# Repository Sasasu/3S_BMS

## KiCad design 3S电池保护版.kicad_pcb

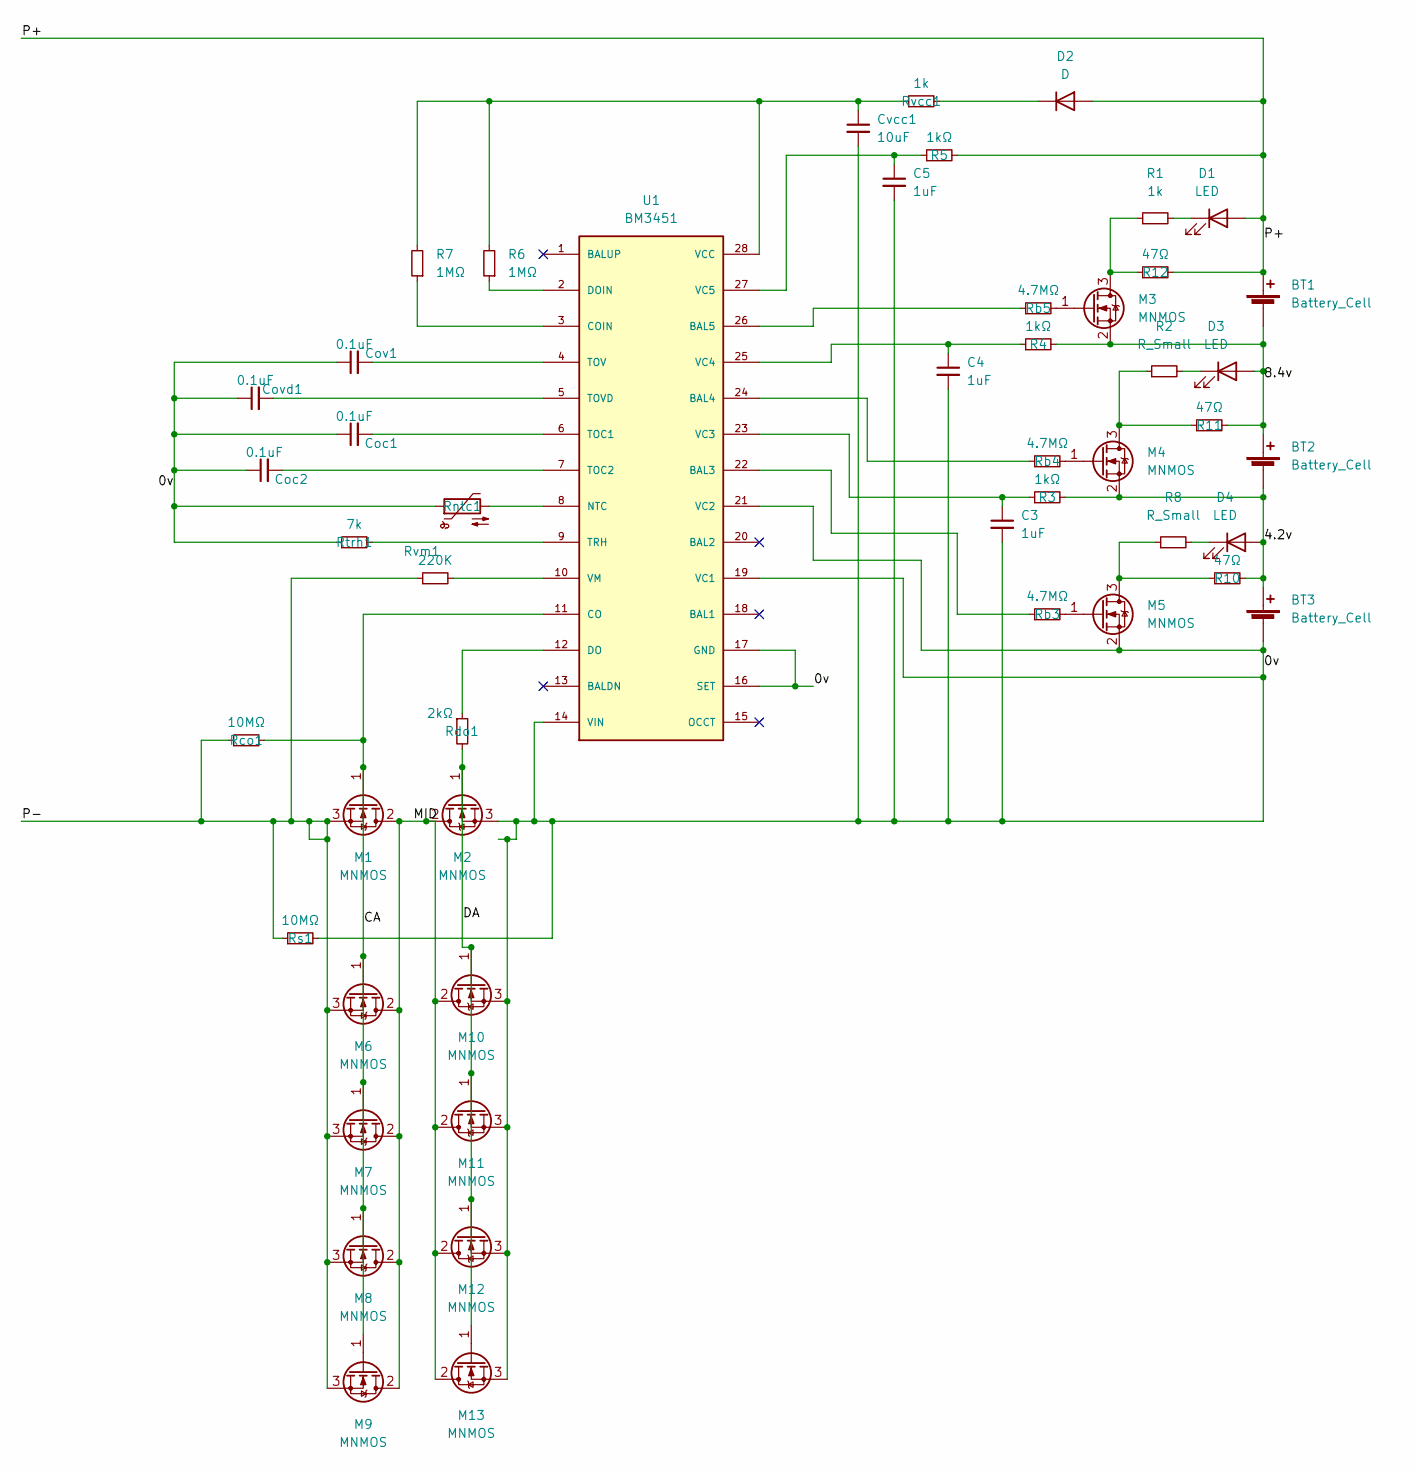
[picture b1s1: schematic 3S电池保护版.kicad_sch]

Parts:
BT1, BT2, BT3: Battery_Cell
C3, C4, C5: 1uF; C_0402_1005Metric_Pad0.74x0.62mm_HandSolder
Coc1, Coc2: 0.1uF; C_0402_1005Metric_Pad0.74x0.62mm_HandSolder
Cov1: 0.1uF; C_0402_1005Metric_Pad0.74x0.62mm_HandSolder
Covd1: 0.1uF; C_0402_1005Metric_Pad0.74x0.62mm_HandSolder
Cvcc1: 10uF; C_0402_1005Metric_Pad0.74x0.62mm_HandSolder
D1, D3, D4: LED; LED_0402_1005Metric_Pad0.77x0.64mm_HandSolder
D2: D; D_SOD-323
M1, M2, M6, M7, M8, M9, M10, M11, M12, M13: MNMOS; TO-252-2
M3, M4, M5: MNMOS; SOT-23
R1: 1k; R_0402_1005Metric_Pad0.72x0.64mm_HandSolder
R2, R8: R_Small; R_0402_1005Metric_Pad0.72x0.64mm_HandSolder
R3, R4, R5: 1kΩ; R_0402_1005Metric_Pad0.72x0.64mm_HandSolder
R6, R7: 1MΩ; R_0402_1005Metric_Pad0.72x0.64mm_HandSolder
R10, R11, R12: 47Ω; R_2512_6332Metric
Rb3, Rb4, Rb5: 4.7MΩ; R_0402_1005Metric_Pad0.72x0.64mm_HandSolder
Rco1: 10MΩ; R_0402_1005Metric_Pad0.72x0.64mm_HandSolder
Rdo1: 2kΩ; R_0402_1005Metric_Pad0.72x0.64mm_HandSolder
Rntc1: Thermistor_NTC; R_0805_2012Metric_Pad1.20x1.40mm_HandSolder
Rs1: 10MΩ; R_0402_1005Metric_Pad0.72x0.64mm_HandSolder
Rtrh1: 7k; R_0402_1005Metric_Pad0.72x0.64mm_HandSolder
Rvcc1: 1k; R_0402_1005Metric_Pad0.72x0.64mm_HandSolder
Rvm1: 220K; R_0402_1005Metric_Pad0.72x0.64mm_HandSolder
U1: BM3451; SSOP28

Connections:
/0v: BT3.2 (-), C3.2, C4.2, C5.2, Coc1.1, Coc2.1, Cov1.1, Covd1.1, Cvcc1.2, M2.3 (S), M5.2 (S), M10.3 (S), M11.3 (S), M12.3 (S), M13.3 (S), Rntc1.1, Rs1.2, Rtrh1.1, U1.14 (VIN), U1.16 (SET), U1.17 (GND), U1.19 (VC1), U1.21 (VC2)
/4.2v: BT2.2 (-), BT3.1 (+), D4.2 (A), M4.2 (S), R3.2, R10.2
/8.4v: BT1.2 (-), BT2.1 (+), D3.2 (A), M3.2 (S), R4.2, R11.2
/CA: M1.1 (G), M6.1 (G), M7.1 (G), M8.1 (G), M9.1 (G), Rco1.2, U1.11 (CO)
/DA: M2.1 (G), M10.1 (G), M11.1 (G), M12.1 (G), M13.1 (G), Rdo1.2
/MID: M1.2 (D), M2.2 (D), M6.2 (D), M7.2 (D), M8.2 (D), M9.2 (D), M10.2 (D), M11.2 (D), M12.2 (D), M13.2 (D)
/P+: BT1.1 (+), D1.2 (A), D2.2 (A), R5.2, R12.2
/P-: M1.3 (S), M6.3 (S), M7.3 (S), M8.3 (S), M9.3 (S), Rco1.1, Rs1.1, Rvm1.1
unnamed: C3.1, R3.1, U1.23 (VC3)
unnamed: C4.1, R4.1, U1.25 (VC4)
unnamed: C5.1, R5.1, U1.27 (VC5)
unnamed: Coc1.2, U1.6 (TOC1)
unnamed: Coc2.2, U1.7 (TOC2)
unnamed: Cov1.2, U1.4 (TOV)
unnamed: Covd1.2, U1.5 (TOVD)
unnamed: Cvcc1.1, R6.2, R7.2, Rvcc1.1, U1.28 (VCC)
unnamed: D1.1 (K), R1.2
unnamed: D2.1 (K), Rvcc1.2
unnamed: D3.1 (K), R2.2
unnamed: D4.1 (K), R8.2
unnamed: M3.1 (G), Rb5.2
unnamed: M3.3 (D), R1.1, R12.1
unnamed: M4.1 (G), Rb4.2
unnamed: M4.3 (D), R2.1, R11.1
unnamed: M5.1 (G), Rb3.2
unnamed: M5.3 (D), R8.1, R10.1
unnamed: R6.1, U1.2 (DOIN)
unnamed: R7.1, U1.3 (COIN)
unnamed: Rb3.1, U1.22 (BAL3)
unnamed: Rb4.1, U1.24 (BAL4)
unnamed: Rb5.1, U1.26 (BAL5)
unnamed: Rdo1.1, U1.12 (DO)
unnamed: Rntc1.2, U1.8 (NTC)
unnamed: Rtrh1.2, U1.9 (TRH)
unnamed: Rvm1.2, U1.10 (VM)

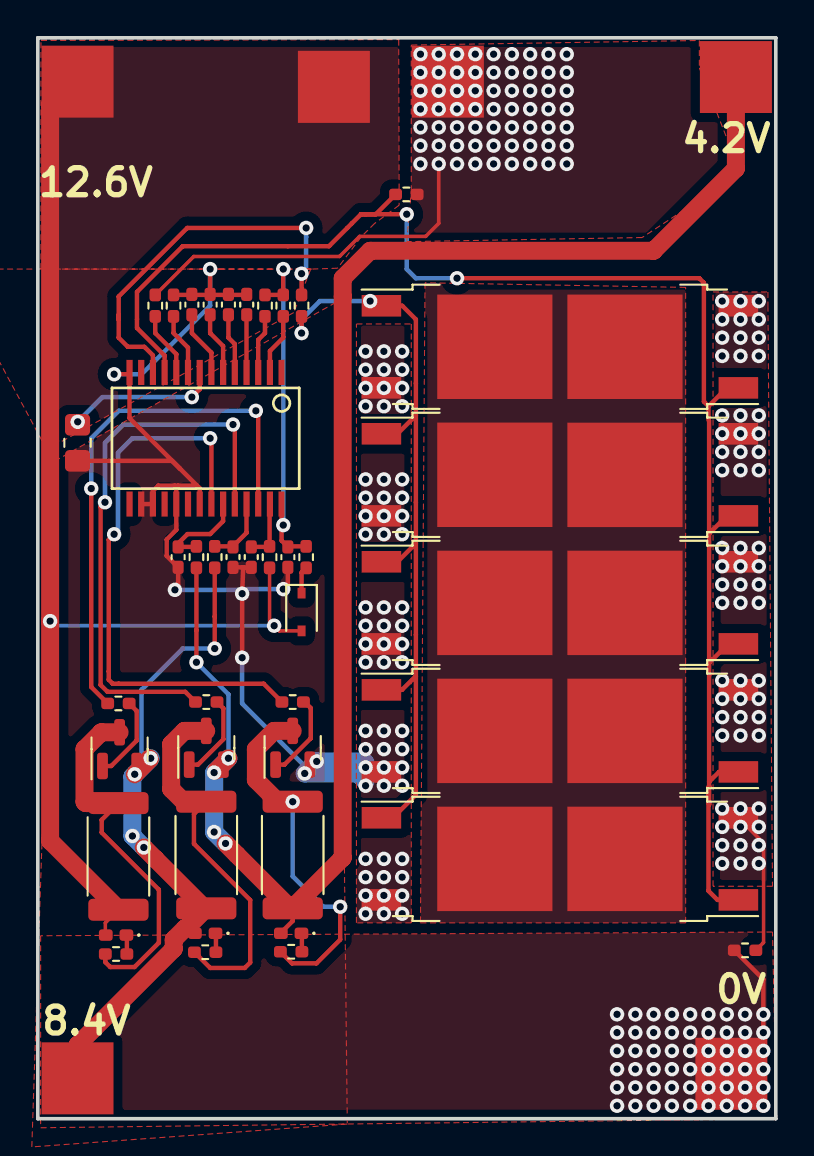
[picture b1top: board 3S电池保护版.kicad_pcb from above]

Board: 2 copper layers, 41.0 x 60.1 mm, 47 parts (0 on the bottom side), 35 nets.

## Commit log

2022-09-05 init
